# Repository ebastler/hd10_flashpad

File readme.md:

# Wurkkos HD10 flashpad adapter PCB

The Wurkkos HD10 is a compact 14500-cell powered 90° angle light running on open source Anduril firmware. The testing units and early batches, however, have the flashing pads hidden away on the inside of the light in an inaccessible spot.

## Ordering
Download the [Gerber files](./fab/HD10_flashpad.zip) from the [fab](./fab) folder and upload them at a PCB factory of your choice. Make sure you will order `0.8 mm` thick PCBs at most. I would recommend even thinner if that does not cost an excessive amount of money. The prototype pictured below is 0.8 mm and works even with flat top cells, but needs you to keep your solder joints very flat. 

PCB factories might check back because the bottom layer has no copper at all, and the PCB has no drills. I used JLCPCB and they asked about both points. Just confirm them to proceed into production - this is intentional.

## Modifying the light
I have posted a more detailed teadown [here](https://budgetlightforum.com/t/review-wurkkos-hd10-a-great-formfactor-anduril-2-90-headlamp/224176/2), so this readme will only outline the basics:

1) First you need to desolder the 6 pins connecting the LED daughterboard to the main PCB. This will allow you to carefully push the driver out of the battery tube. Desoldering pumps and solder wick are a great help for this step, and a moderately powerful soldering iron is needed. 

2) Locate the flashing pads, and solder a thin enameled wire to it. Please do not use bare copper wire (it will short the light) or regular wire (too thick). Route the wire through the hole for the LED daughterboard. This milled slot has drilled corners, which are large enough for a thin enameled wire to pass through. Cover the solder joint and wire with a bit of Kapton tape.

3) Reassemble the light, and make sure the wire stays in one of the corner drills. On the picture I soldered it to a temporary pad of copper tape on Kapton - ignore that step since you will have the PCBs already.

4) Place the PCB as shown and stick it down with a thin double sided tape. The PCB has no metal on the bottom layer, so it can not short out anything. Solder the thin wire to the `R` pad, and the `+` and `-` pads to the nearest contacts on the LED PCB. A short piece of (very) thin wire might make this easier. You might consider adding a final layer of Kapton over all exposed solder joints as a last step and make sure they are all flat enough that they do not protrude over the brass button.

| <div style="width:350px"></div> | <div style="width:350px"></div> |
|:----------------------------------------------------|:--------------------------------------------------------------|
|  |  |
| 1) Remove PCB from housing | 2) Solder data wire |
|  | |
| 3) Reassemble | 4) Add flashing PCB |

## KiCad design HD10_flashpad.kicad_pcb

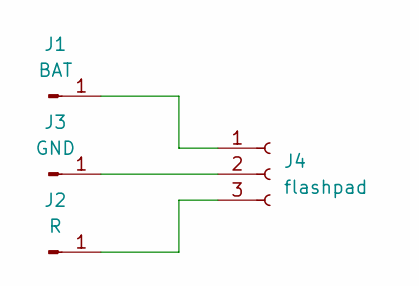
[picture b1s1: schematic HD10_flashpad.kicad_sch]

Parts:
J1: BAT; TestPoint_Pad_D2.0mm
J2: R; TestPoint_Pad_D2.0mm
J3: GND; TestPoint_Pad_1.0x1.0mm
J4: flashpad; flashpads

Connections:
unnamed: J1.1, J4.1
unnamed: J2.1, J4.3
unnamed: J3.1, J4.2

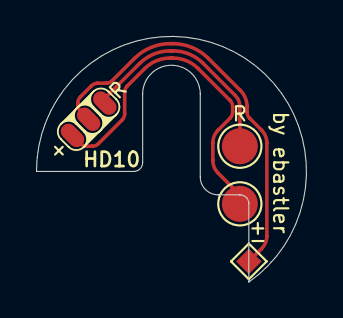
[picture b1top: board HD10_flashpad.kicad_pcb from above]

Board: 2 copper layers, 15.0 x 13.6 mm, 4 parts (0 on the bottom side), 3 nets.

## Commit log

2024-07-06 improved table
